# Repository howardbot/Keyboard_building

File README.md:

# Keyboard_building

## Library Required
Footprint: [ebastler/marbastlib](https://github.com/ebastler/marbastlib)

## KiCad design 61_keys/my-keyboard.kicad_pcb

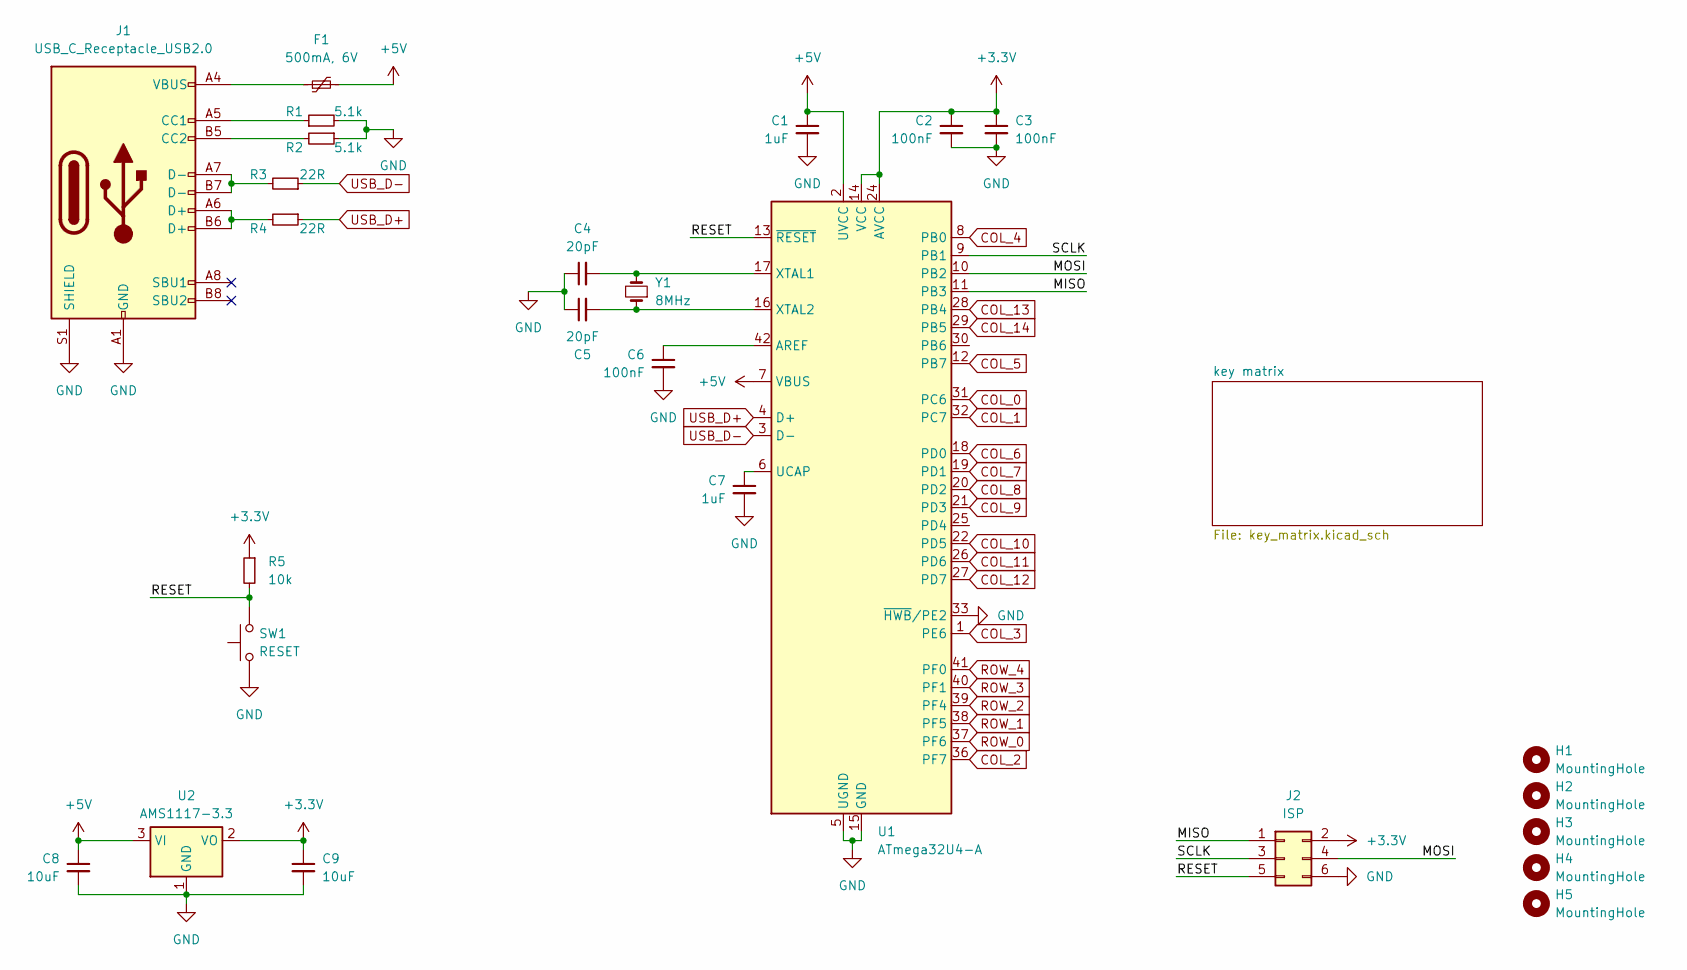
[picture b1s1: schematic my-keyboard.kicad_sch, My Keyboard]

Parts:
C1, C7: 1uF; C_0603_1608Metric
C2, C3, C6: 100nF; C_0603_1608Metric
C4, C5: 20pF; C_0603_1608Metric
C8, C9: 10uF; C_0603_1608Metric
F1: 500mA, 6V; Fuse_0805_2012Metric
H1, H2, H3, H4, H5: MountingHole; MountingHole_3.2mm_M3
J1: USB_C_Receptacle_USB2.0; USB_C_Receptacle_HRO_TYPE-C-31-M-12
J2: ISP; PinHeader_2x03_P2.54mm_Vertical
R1, R2: 5.1k; R_0603_1608Metric
R3, R4: 22R; R_0603_1608Metric
R5: 10k; R_0603_1608Metric
SW1: RESET; SW_SPST_CK_RS282G05A3
U1: ATmega32U4-A; TQFP-44_10x10mm_P0.8mm
U2: AMS1117-3.3; SOT-223-3_TabPin2
Y1: 8MHz; Crystal_SMD_3215-2Pin_3.2x1.5mm

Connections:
+3.3V: C2.1, C3.1, C9.1, J2.2, R5.1, U1.14 (VCC), U1.24 (AVCC), U1.34 (VCC), U1.44 (AVCC), U2.2 (VO)
+5V: C1.1, C8.1, F1.2, U1.2 (UVCC), U1.7 (VBUS), U2.3 (VI)
/MISO: J2.1, U1.11 (PB3)
/MOSI: J2.4, U1.10 (PB2)
/RESET: J2.5, R5.2, SW1.2, U1.13 (~RESET)
/SCLK: J2.3, U1.9 (PB1)
COL_0: U1.31 (PC6); also elsewhere on the board
COL_1: U1.32 (PC7); also elsewhere on the board
COL_2: U1.36 (PF7); also elsewhere on the board
COL_3: U1.1 (PE6); also elsewhere on the board
COL_4: U1.8 (PB0); also elsewhere on the board
COL_5: U1.12 (PB7); also elsewhere on the board
COL_6: U1.18 (PD0); also elsewhere on the board
COL_7: U1.19 (PD1); also elsewhere on the board
COL_8: U1.20 (PD2); also elsewhere on the board
COL_9: U1.21 (PD3); also elsewhere on the board
COL_10: U1.22 (PD5); also elsewhere on the board
COL_11: U1.26 (PD6); also elsewhere on the board
COL_12: U1.27 (PD7); also elsewhere on the board
COL_13: U1.28 (PB4); also elsewhere on the board
COL_14: U1.29 (PB5); also elsewhere on the board
GND: C1.2, C2.2, C3.2, C4.1, C5.1, C6.2, C7.2, C8.2, C9.2, J1.A1 (GND), J1.A12 (GND), J1.B1 (GND), J1.B12 (GND), J1.S1 (SHIELD), J2.6, R1.2, R2.1, SW1.1, U1.5 (UGND), U1.15 (GND), U1.23 (GND), U1.33 (~HWB/PE2), U1.35 (GND), U1.43 (GND), U2.1 (GND)
unnamed: F1.1, J1.A4 (VBUS), J1.A9 (VBUS), J1.B4 (VBUS), J1.B9 (VBUS)
unnamed: J1.A5 (CC1), R1.1
unnamed: J1.B5 (CC2), R2.2
unnamed: J1.A6 (D+), J1.B6 (D+), R4.2
unnamed: J1.A7 (D-), J1.B7 (D-), R3.2
unnamed: C6.1, U1.42 (AREF)
unnamed: C7.1, U1.6 (UCAP)
unnamed: C4.2, U1.17 (XTAL1), Y1.2
unnamed: C5.2, U1.16 (XTAL2), Y1.1
ROW_0: U1.37 (PF6); also elsewhere on the board
ROW_1: U1.38 (PF5); also elsewhere on the board
ROW_2: U1.39 (PF4); also elsewhere on the board
ROW_3: U1.40 (PF1); also elsewhere on the board
ROW_4: U1.41 (PF0); also elsewhere on the board
USB_D+: R4.1, U1.4 (D+)
USB_D-: R3.1, U1.3 (D-)

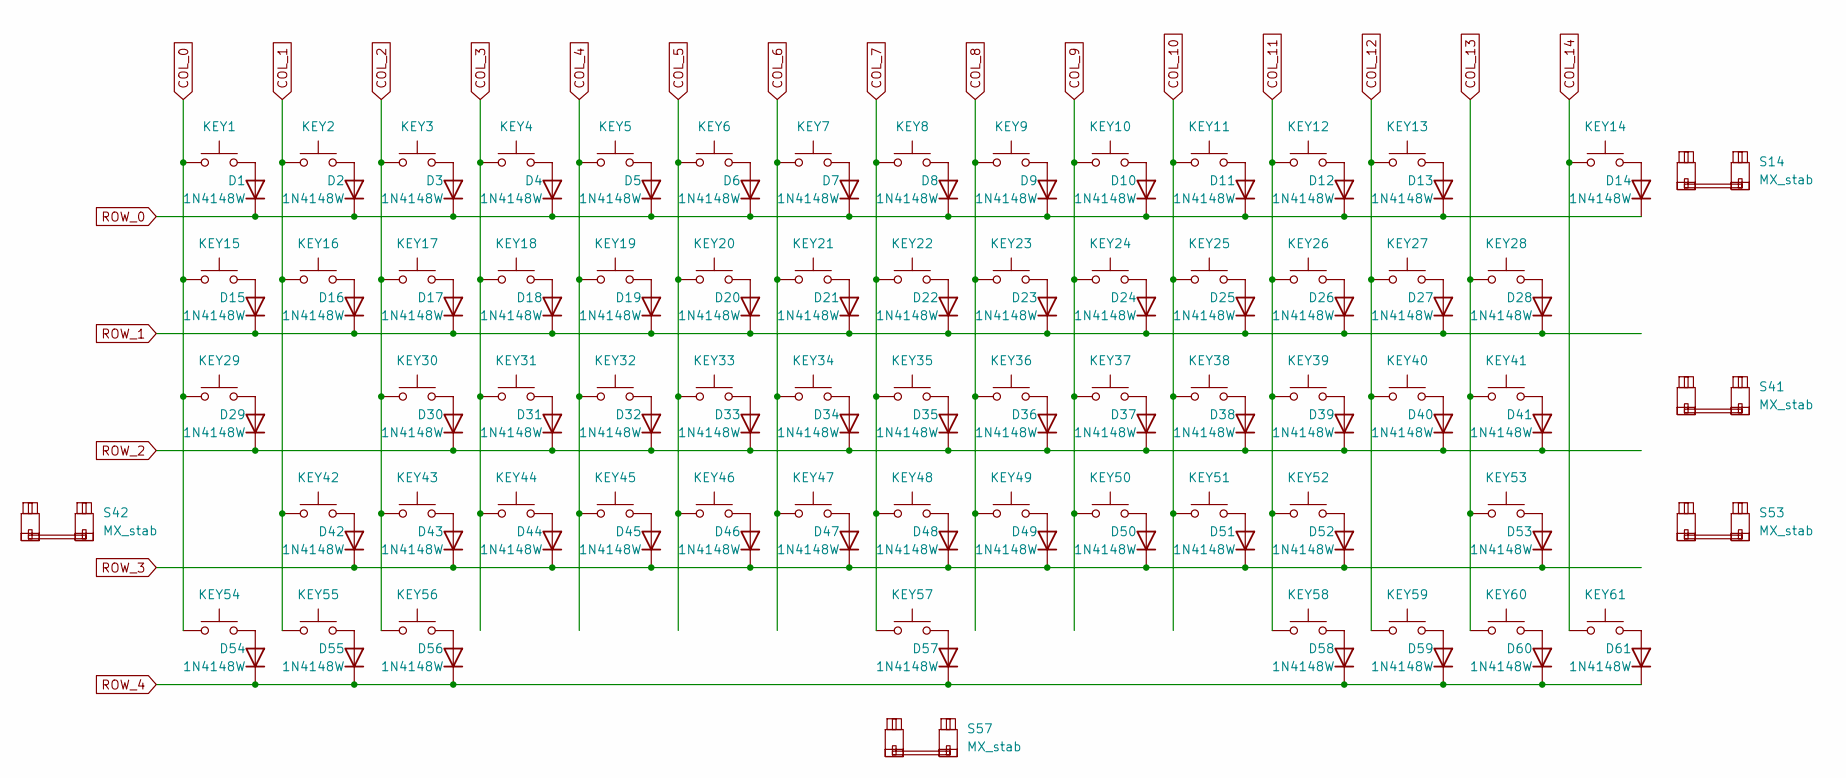
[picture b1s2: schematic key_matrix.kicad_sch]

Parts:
D1, D2, D3, D4, D5, D6, D7, D8, D9, D10, D11, D12, D13, D14, D15, D16, D17, D18, D19, D20, D21, D22, D23, D24, D25, D26, D27, D28, D29, D30, D31, D32, D33, D34, D35, D36, D37, D38, D39, D40, D41, D42, D43, D44, D45, D46, D47, D48, D49, D50, D51, D52, D53, D54, D55, D56, D57, D58, D59, D60, D61: 1N4148W; D_SOD-123
KEY1, KEY2, KEY3, KEY4, KEY5, KEY6, KEY7, KEY8, KEY9, KEY10, KEY11, KEY12, KEY13, KEY14, KEY15, KEY16, KEY17, KEY18, KEY19, KEY20, KEY21, KEY22, KEY23, KEY24, KEY25, KEY26, KEY27, KEY28, KEY29, KEY30, KEY31, KEY32, KEY33, KEY34, KEY35, KEY36, KEY37, KEY38, KEY39, KEY40, KEY41, KEY42, KEY43, KEY44, KEY45, KEY46, KEY47, KEY48, KEY49, KEY50, KEY51, KEY52, KEY53, KEY54, KEY55, KEY56, KEY57, KEY58, KEY59, KEY60, KEY61: SW_Push; SW_MX_HotSwap_PTH
S14: MX_stab; STAB_MX_P_2u
S41, S42: MX_stab; STAB_MX_P_2.25u
S53: MX_stab; STAB_MX_P_2.75u
S57: MX_stab; STAB_MX_P_6.25u

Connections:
COL_0: KEY1.1, KEY15.1, KEY29.1, KEY54.1; also elsewhere on the board
COL_1: KEY2.1, KEY16.1, KEY42.1, KEY55.1; also elsewhere on the board
COL_2: KEY3.1, KEY17.1, KEY30.1, KEY43.1, KEY56.1; also elsewhere on the board
COL_3: KEY4.1, KEY18.1, KEY31.1, KEY44.1; also elsewhere on the board
COL_4: KEY5.1, KEY19.1, KEY32.1, KEY45.1; also elsewhere on the board
COL_5: KEY6.1, KEY20.1, KEY33.1, KEY46.1; also elsewhere on the board
COL_6: KEY7.1, KEY21.1, KEY34.1, KEY47.1; also elsewhere on the board
COL_7: KEY8.1, KEY22.1, KEY35.1, KEY48.1, KEY57.1; also elsewhere on the board
COL_8: KEY9.1, KEY23.1, KEY36.1, KEY49.1; also elsewhere on the board
COL_9: KEY10.1, KEY24.1, KEY37.1, KEY50.1; also elsewhere on the board
COL_10: KEY11.1, KEY25.1, KEY38.1, KEY51.1; also elsewhere on the board
COL_11: KEY12.1, KEY26.1, KEY39.1, KEY52.1, KEY58.1; also elsewhere on the board
COL_12: KEY13.1, KEY27.1, KEY40.1, KEY59.1; also elsewhere on the board
COL_13: KEY28.1, KEY41.1, KEY53.1, KEY60.1; also elsewhere on the board
COL_14: KEY14.1, KEY61.1; also elsewhere on the board
unnamed: D1.2 (A), KEY1.2
unnamed: D2.2 (A), KEY2.2
unnamed: D3.2 (A), KEY3.2
unnamed: D4.2 (A), KEY4.2
unnamed: D5.2 (A), KEY5.2
unnamed: D6.2 (A), KEY6.2
unnamed: D7.2 (A), KEY7.2
unnamed: D8.2 (A), KEY8.2
unnamed: D9.2 (A), KEY9.2
unnamed: D10.2 (A), KEY10.2
unnamed: D11.2 (A), KEY11.2
unnamed: D12.2 (A), KEY12.2
unnamed: D13.2 (A), KEY13.2
unnamed: D14.2 (A), KEY14.2
unnamed: D15.2 (A), KEY15.2
unnamed: D16.2 (A), KEY16.2
unnamed: D17.2 (A), KEY17.2
unnamed: D18.2 (A), KEY18.2
unnamed: D19.2 (A), KEY19.2
unnamed: D20.2 (A), KEY20.2
unnamed: D21.2 (A), KEY21.2
unnamed: D22.2 (A), KEY22.2
unnamed: D23.2 (A), KEY23.2
unnamed: D24.2 (A), KEY24.2
unnamed: D25.2 (A), KEY25.2
unnamed: D26.2 (A), KEY26.2
unnamed: D27.2 (A), KEY27.2
unnamed: D28.2 (A), KEY28.2
unnamed: D29.2 (A), KEY29.2
unnamed: D30.2 (A), KEY30.2
unnamed: D31.2 (A), KEY31.2
unnamed: D32.2 (A), KEY32.2
unnamed: D33.2 (A), KEY33.2
unnamed: D34.2 (A), KEY34.2
unnamed: D35.2 (A), KEY35.2
unnamed: D36.2 (A), KEY36.2
unnamed: D37.2 (A), KEY37.2
unnamed: D38.2 (A), KEY38.2
unnamed: D39.2 (A), KEY39.2
unnamed: D40.2 (A), KEY40.2
unnamed: D41.2 (A), KEY41.2
unnamed: D42.2 (A), KEY42.2
unnamed: D43.2 (A), KEY43.2
unnamed: D44.2 (A), KEY44.2
unnamed: D45.2 (A), KEY45.2
unnamed: D46.2 (A), KEY46.2
unnamed: D47.2 (A), KEY47.2
unnamed: D48.2 (A), KEY48.2
unnamed: D49.2 (A), KEY49.2
unnamed: D50.2 (A), KEY50.2
unnamed: D51.2 (A), KEY51.2
unnamed: D52.2 (A), KEY52.2
unnamed: D53.2 (A), KEY53.2
unnamed: D54.2 (A), KEY54.2
unnamed: D55.2 (A), KEY55.2
unnamed: D56.2 (A), KEY56.2
unnamed: D57.2 (A), KEY57.2
unnamed: D58.2 (A), KEY58.2
unnamed: D59.2 (A), KEY59.2
unnamed: D60.2 (A), KEY60.2
unnamed: D61.2 (A), KEY61.2
ROW_0: D1.1 (K), D2.1 (K), D3.1 (K), D4.1 (K), D5.1 (K), D6.1 (K), D7.1 (K), D8.1 (K), D9.1 (K), D10.1 (K), D11.1 (K), D12.1 (K), D13.1 (K), D14.1 (K); also elsewhere on the board
ROW_1: D15.1 (K), D16.1 (K), D17.1 (K), D18.1 (K), D19.1 (K), D20.1 (K), D21.1 (K), D22.1 (K), D23.1 (K), D24.1 (K), D25.1 (K), D26.1 (K), D27.1 (K), D28.1 (K); also elsewhere on the board
ROW_2: D29.1 (K), D30.1 (K), D31.1 (K), D32.1 (K), D33.1 (K), D34.1 (K), D35.1 (K), D36.1 (K), D37.1 (K), D38.1 (K), D39.1 (K), D40.1 (K), D41.1 (K); also elsewhere on the board
ROW_3: D42.1 (K), D43.1 (K), D44.1 (K), D45.1 (K), D46.1 (K), D47.1 (K), D48.1 (K), D49.1 (K), D50.1 (K), D51.1 (K), D52.1 (K), D53.1 (K); also elsewhere on the board
ROW_4: D54.1 (K), D55.1 (K), D56.1 (K), D57.1 (K), D58.1 (K), D59.1 (K), D60.1 (K), D61.1 (K); also elsewhere on the board

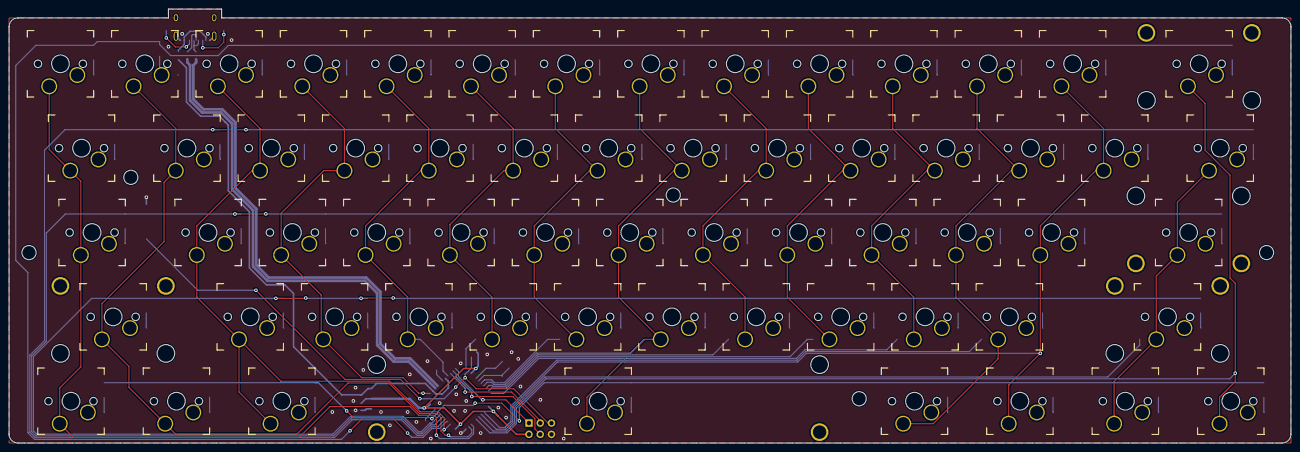
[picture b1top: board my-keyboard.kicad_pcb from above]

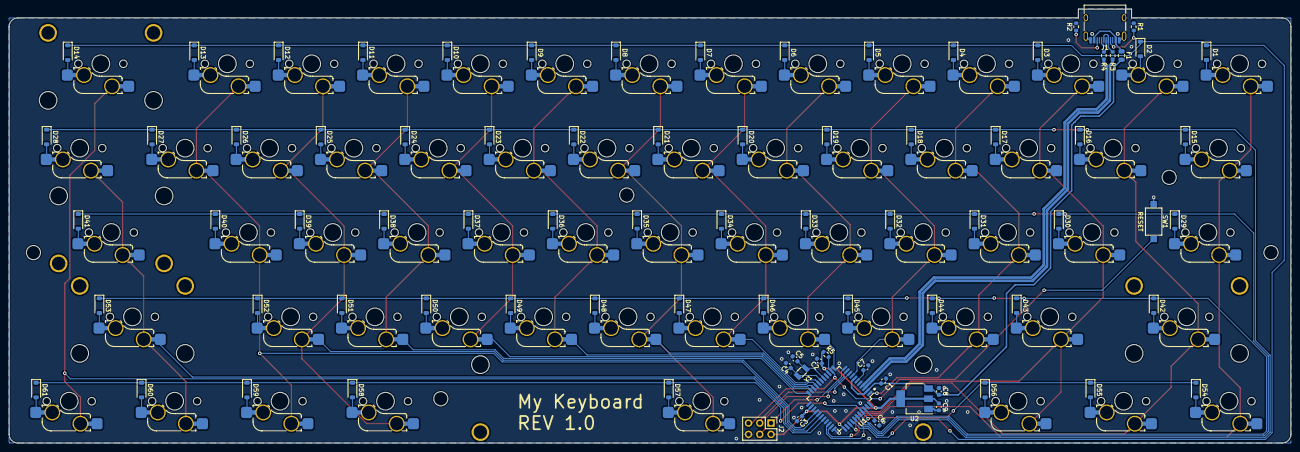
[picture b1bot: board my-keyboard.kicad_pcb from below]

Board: 2 copper layers, 289.5 x 98.0 mm, 153 parts (87 on the bottom side), 99 nets.

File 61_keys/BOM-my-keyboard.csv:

Comment,Designator,Footprint,LCSC,Quantity
SW_Push,KEY4,SW_MX_HotSwap_PTH,,1
MX_stab,S41,STAB_MX_P_2.25u,,1
SW_Push,KEY16,SW_MX_HotSwap_PTH,,1
SW_Push,KEY47,SW_MX_HotSwap_PTH,,1
SW_Push,KEY45,SW_MX_HotSwap_PTH,,1
SW_Push,KEY48,SW_MX_HotSwap_PTH,,1
SW_Push,KEY59,SW_MX_HotSwap_PTH,,1
SW_Push,KEY21,SW_MX_HotSwap_PTH,,1
SW_Push,KEY58,SW_MX_HotSwap_PTH,,1
SW_Push,KEY32,SW_MX_HotSwap_PTH,,1
SW_Push,KEY6,SW_MX_HotSwap_PTH,,1
SW_Push,KEY53,SW_MX_HotSwap_PTH,,1
SW_Push,KEY26,SW_MX_HotSwap_PTH,,1
SW_Push,KEY15,SW_MX_HotSwap_PTH,,1
SW_Push,KEY55,SW_MX_HotSwap_PTH,,1
SW_Push,KEY29,SW_MX_HotSwap_PTH,,1
SW_Push,KEY46,SW_MX_HotSwap_PTH,,1
SW_Push,KEY35,SW_MX_HotSwap_PTH,,1
SW_Push,KEY31,SW_MX_HotSwap_PTH,,1
SW_Push,KEY19,SW_MX_HotSwap_PTH,,1
SW_Push,KEY8,SW_MX_HotSwap_PTH,,1
SW_Push,KEY37,SW_MX_HotSwap_PTH,,1
MX_stab,S57,STAB_MX_P_6.25u,,1
SW_Push,KEY54,SW_MX_HotSwap_PTH,,1
SW_Push,KEY23,SW_MX_HotSwap_PTH,,1
SW_Push,KEY17,SW_MX_HotSwap_PTH,,1
SW_Push,KEY7,SW_MX_HotSwap_PTH,,1
SW_Push,KEY11,SW_MX_HotSwap_PTH,,1
SW_Push,KEY60,SW_MX_HotSwap_PTH,,1
SW_Push,KEY51,SW_MX_HotSwap_PTH,,1
SW_Push,KEY25,SW_MX_HotSwap_PTH,,1
SW_Push,KEY9,SW_MX_HotSwap_PTH,,1
MX_stab,S42,STAB_MX_P_2.25u,,1
SW_Push,KEY30,SW_MX_HotSwap_PTH,,1
SW_Push,KEY42,SW_MX_HotSwap_PTH,,1
SW_Push,KEY22,SW_MX_HotSwap_PTH,,1
MX_stab,S53,STAB_MX_P_2.75u,,1
SW_Push,KEY27,SW_MX_HotSwap_PTH,,1
SW_Push,KEY33,SW_MX_HotSwap_PTH,,1
SW_Push,KEY14,SW_MX_HotSwap_PTH,,1
SW_Push,KEY41,SW_MX_HotSwap_PTH,,1
SW_Push,KEY28,SW_MX_HotSwap_PTH,,1
SW_Push,KEY18,SW_MX_HotSwap_PTH,,1
SW_Push,KEY57,SW_MX_HotSwap_PTH,,1
SW_Push,KEY61,SW_MX_HotSwap_PTH,,1
SW_Push,KEY40,SW_MX_HotSwap_PTH,,1
SW_Push,KEY5,SW_MX_HotSwap_PTH,,1
MX_stab,S14,STAB_MX_P_2u,,1
SW_Push,KEY3,SW_MX_HotSwap_PTH,,1
SW_Push,KEY52,SW_MX_HotSwap_PTH,,1
SW_Push,KEY56,SW_MX_HotSwap_PTH,,1
SW_Push,KEY20,SW_MX_HotSwap_PTH,,1
SW_Push,KEY12,SW_MX_HotSwap_PTH,,1
SW_Push,KEY39,SW_MX_HotSwap_PTH,,1
SW_Push,KEY1,SW_MX_HotSwap_PTH,,1
SW_Push,KEY24,SW_MX_HotSwap_PTH,,1
SW_Push,KEY43,SW_MX_HotSwap_PTH,,1
SW_Push,KEY50,SW_MX_HotSwap_PTH,,1
SW_Push,KEY13,SW_MX_HotSwap_PTH,,1
SW_Push,KEY10,SW_MX_HotSwap_PTH,,1
SW_Push,KEY49,SW_MX_HotSwap_PTH,,1
SW_Push,KEY2,SW_MX_HotSwap_PTH,,1
SW_Push,KEY38,SW_MX_HotSwap_PTH,,1
SW_Push,KEY44,SW_MX_HotSwap_PTH,,1
SW_Push,KEY34,SW_MX_HotSwap_PTH,,1
SW_Push,KEY36,SW_MX_HotSwap_PTH,,1
1N4148W,D26,D_SOD-123,,1
1N4148W,D24,D_SOD-123,,1
1N4148W,D55,D_SOD-123,,1
1N4148W,D28,D_SOD-123,,1
1N4148W,D38,D_SOD-123,,1
ISP,J2,PinHeader_2x03_P2.54mm_Vertical,,1
1N4148W,D18,D_SOD-123,,1
1N4148W,D51,D_SOD-123,,1
1N4148W,D10,D_SOD-123,,1
1N4148W,D45,D_SOD-123,,1
1N4148W,D8,D_SOD-123,,1
20pF,C5,C_0603_1608Metric,,1
1N4148W,D49,D_SOD-123,,1
1N4148W,D1,D_SOD-123,,1
1N4148W,D4,D_SOD-123,,1
100nF,C2,C_0603_1608Metric,,1
22R,R3,R_0603_1608Metric,,1
1N4148W,D2,D_SOD-123,,1
1N4148W,D61,D_SOD-123,,1
1N4148W,D46,D_SOD-123,,1
1N4148W,D3,D_SOD-123,,1
100nF,C6,C_0603_1608Metric,,1
MountingHole,H2,MountingHole_3.2mm_M3,,1
5.1k,R1,R_0603_1608Metric,,1
1N4148W,D23,D_SOD-123,,1
1N4148W,D32,D_SOD-123,,1
1N4148W,D17,D_SOD-123,,1
1N4148W,D39,D_SOD-123,,1
ATmega32U4-A,U1,TQFP-44_10x10mm_P0.8mm,,1
1N4148W,D11,D_SOD-123,,1
1N4148W,D58,D_SOD-123,,1
10k,R5,R_0603_1608Metric,,1
1N4148W,D30,D_SOD-123,,1
1N4148W,D43,D_SOD-123,,1
1N4148W,D48,D_SOD-123,,1
1N4148W,D57,D_SOD-123,,1
1N4148W,D52,D_SOD-123,,1
1N4148W,D29,D_SOD-123,,1
MountingHole,H1,MountingHole_3.2mm_M3,,1
MountingHole,H5,MountingHole_3.2mm_M3,,1
1N4148W,D16,D_SOD-123,,1
5.1k,R2,R_0603_1608Metric,,1
1uF,C7,C_0603_1608Metric,,1
20pF,C4,C_0603_1608Metric,,1
1N4148W,D60,D_SOD-123,,1
1N4148W,D7,D_SOD-123,,1
1N4148W,D44,D_SOD-123,,1
1N4148W,D40,D_SOD-123,,1
1N4148W,D53,D_SOD-123,,1
10uF,C9,C_0603_1608Metric,,1
1N4148W,D36,D_SOD-123,,1
1N4148W,D9,D_SOD-123,,1
8MHz,Y1,Crystal_SMD_3215-2Pin_3.2x1.5mm,,1
"500mA, 6V",F1,Fuse_0805_2012Metric,,1
10uF,C8,C_0603_1608Metric,,1
1N4148W,D27,D_SOD-123,,1
1N4148W,D41,D_SOD-123,,1
RESET,SW1,SW_SPST_CK_RS282G05A3,,1
USB_C_Receptacle_USB2.0,J1,USB_C_Receptacle_HRO_TYPE-C-31-M-12,,1
1N4148W,D15,D_SOD-123,,1
1N4148W,D42,D_SOD-123,,1
1N4148W,D25,D_SOD-123,,1
1N4148W,D54,D_SOD-123,,1
1uF,C1,C_0603_1608Metric,,1
1N4148W,D19,D_SOD-123,,1
22R,R4,R_0603_1608Metric,,1
1N4148W,D50,D_SOD-123,,1
1N4148W,D20,D_SOD-123,,1
1N4148W,D12,D_SOD-123,,1
1N4148W,D35,D_SOD-123,,1
1N4148W,D56,D_SOD-123,,1
1N4148W,D5,D_SOD-123,,1
1N4148W,D22,D_SOD-123,,1
1N4148W,D34,D_SOD-123,,1
1N4148W,D14,D_SOD-123,,1
1N4148W,D6,D_SOD-123,,1
AMS1117-3.3,U2,SOT-223-3_TabPin2,,1
1N4148W,D21,D_SOD-123,,1
100nF,C3,C_0603_1608Metric,,1
MountingHole,H4,MountingHole_3.2mm_M3,,1
1N4148W,D13,D_SOD-123,,1
1N4148W,D31,D_SOD-123,,1
MountingHole,H3,MountingHole_3.2mm_M3,,1
1N4148W,D33,D_SOD-123,,1
1N4148W,D47,D_SOD-123,,1
1N4148W,D59,D_SOD-123,,1
1N4148W,D37,D_SOD-123,,1

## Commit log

2025-08-02 basic file uploaded
2025-08-02 3D Deomo pics upload
2025-08-02 Create LICENSE_ORIGINAL
2025-08-06 Plate drawing update
